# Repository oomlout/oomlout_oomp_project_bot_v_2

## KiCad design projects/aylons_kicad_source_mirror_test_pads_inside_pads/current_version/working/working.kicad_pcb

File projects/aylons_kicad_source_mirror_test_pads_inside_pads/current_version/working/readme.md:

# kicad_source_mirror
 
## summary 
* id: aylons_kicad_source_mirror_test_pads_inside_pads
* user: aylons
* name: kicad_source_mirror
* board: test_pads_inside_pads
* repo: https://github.com/aylons/kicad-source-mirror
* src_file_repo_kicad_pcb: demos/test_pads_inside_pads/test_pads_inside_pads.kicad_pcb
* src_file_repo_kicad_pcb_link: https://github.com/aylons/kicad-source-mirror/tree/master/demos/test_pads_inside_pads/test_pads_inside_pads.kicad_pcb

* src_file_repo_sch: demos/test_pads_inside_pads/test_pads_inside_pads.sch
* src_file_repo_sch_link: https://github.com/aylons/kicad-source-mirror/tree/master/demos/test_pads_inside_pads/test_pads_inside_pads.sch
* full details link: https://github.com/oomlout/oomlout_oomp_project_bot_v_2/tree/main/projects/aylons_kicad_source_mirror_test_pads_inside_pads/current_version/working

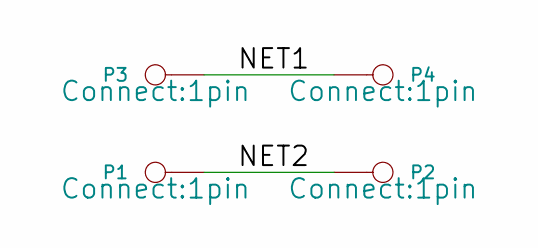
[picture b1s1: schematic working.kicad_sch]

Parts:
P1, P2, P3, P4: CONN_1; 1pin

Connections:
/NET1: P3.1, P4.1
/NET2: P1.1, P2.1

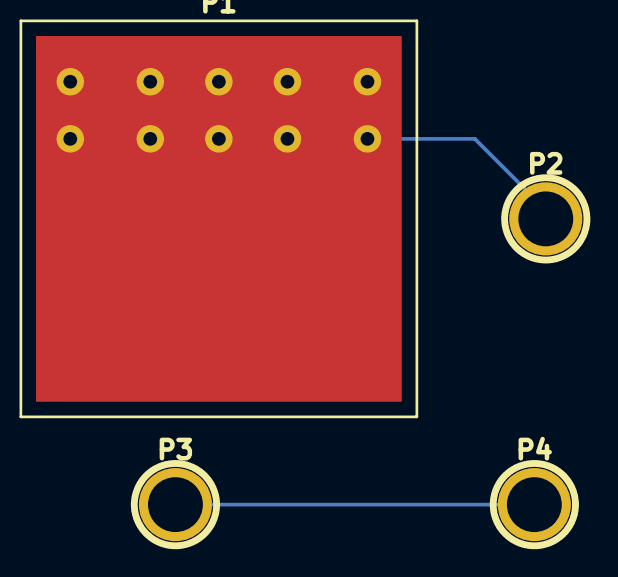
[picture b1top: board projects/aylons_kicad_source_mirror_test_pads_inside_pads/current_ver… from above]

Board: 2 copper layers, 4 parts (0 on the bottom side), 2 nets.

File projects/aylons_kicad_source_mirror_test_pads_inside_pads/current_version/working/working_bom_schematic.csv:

"Source:","C:\gh\oomlout_oomp_project_bot_v_2\projects\aylons_kicad_source_mirror_test_pads_inside_pads\current_version\working\working.kicad_sch"
"Date:","27/09/2023 15:33:38"
"Tool:","Eeschema 7.0.6"
"Generator:","C:/Program Files/KiCad/7.0/bin/scripting/plugins/bom_csv_grouped_by_value_with_fp.py"
"Component Count:","4"
"Ref","Qnty","Value","Cmp name","Footprint","Description","Vendor","DNP"
"P1, P2, P3, P4","4","CONN_1","CONN_1","Connect:1pin","","",""

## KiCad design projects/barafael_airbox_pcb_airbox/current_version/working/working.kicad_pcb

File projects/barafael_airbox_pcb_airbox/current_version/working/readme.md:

# airbox_pcb
 
## summary 
* id: barafael_airbox_pcb_airbox
* user: barafael
* name: airbox_pcb
* board: airbox
* repo: https://github.com/barafael/airbox-pcb
* src_file_repo_kicad_pcb: airbox.kicad_pcb
* src_file_repo_kicad_pcb_link: https://github.com/barafael/airbox-pcb/tree/main/airbox.kicad_pcb

* src_file_repo_sch: airbox.sch
* src_file_repo_sch_link: https://github.com/barafael/airbox-pcb/tree/main/airbox.sch
* full details link: https://github.com/oomlout/oomlout_oomp_project_bot_v_2/tree/main/projects/barafael_airbox_pcb_airbox/current_version/working

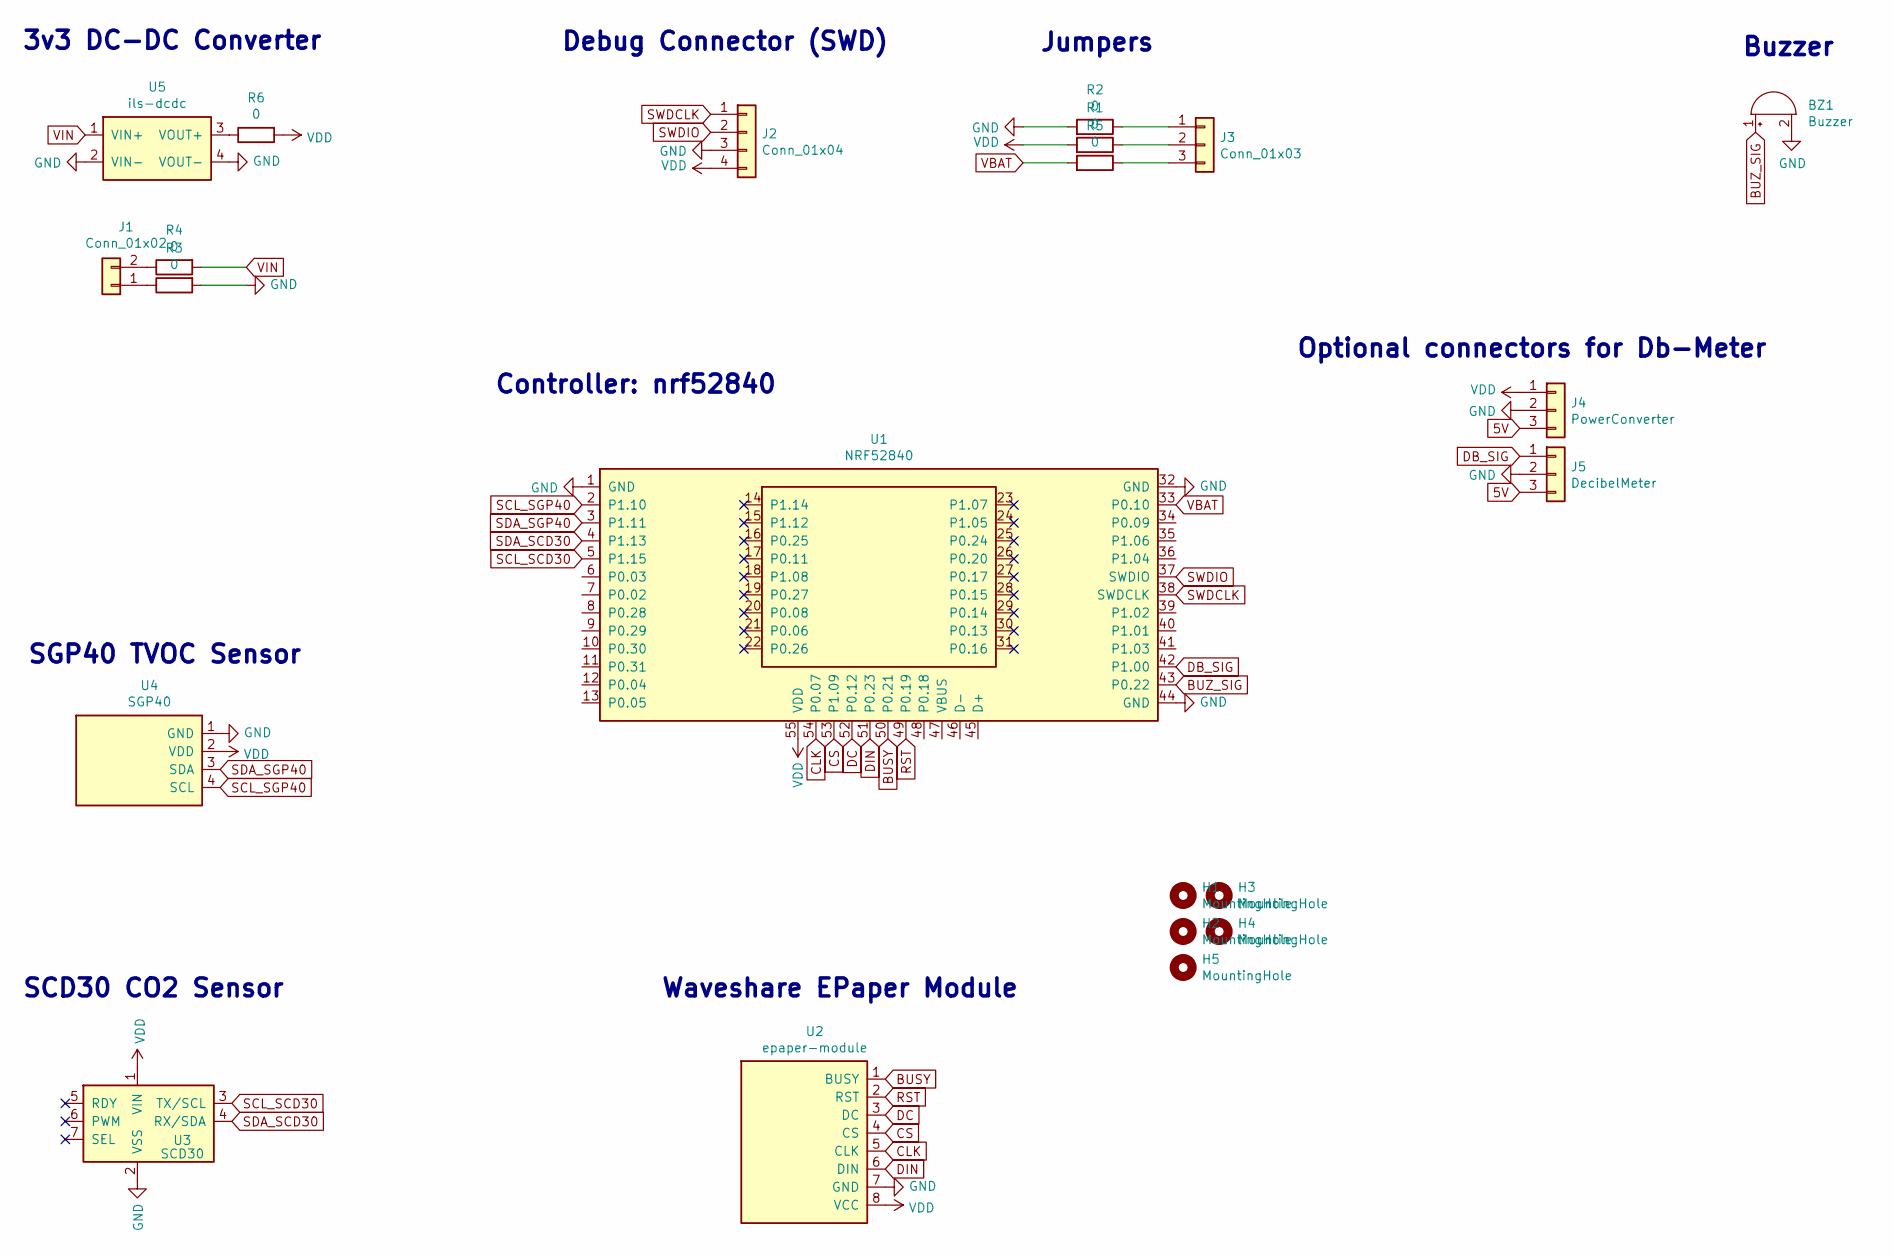
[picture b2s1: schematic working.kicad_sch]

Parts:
BZ1: Buzzer; PS1240P02BT
H1, H2, H3, H4, H5: MountingHole; MountingHole_3mm
J1: Conn_01x02; JST_EH_B2B-EH-A_1x02_P2.50mm_Vertical
J2: Conn_01x04; JST_EH_B4B-EH-A_1x04_P2.50mm_Vertical
J3: Conn_01x03; JST_EH_B3B-EH-A_1x03_P2.50mm_Vertical
J4: PowerConverter; PinSocket_1x03_P2.54mm_Vertical
J5: DecibelMeter; PinSocket_1x03_P2.54mm_Vertical
R1, R2, R3, R4, R5, R6: 0; R_0805_2012Metric
U1: NRF52840; nrf52-waveshare
U2: epaper-module
U3: SCD30; scd30
U4: SGP40; sgp40-sparkx-breakout
U5: ils-dcdc; ils-3v3dcdc

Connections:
5V: J4.3, J5.3
BUSY: U1.50 (P0.21), U2.1 (BUSY)
BUZ_SIG: BZ1.1 (-), U1.43 (P0.22)
CLK: U1.54 (P0.07), U2.5 (CLK)
CS: U1.53 (P1.09), U2.4 (CS)
DB_SIG: J5.1, U1.42 (P1.00)
DC: U1.52 (P0.12), U2.3 (DC)
DIN: U1.51 (P0.23), U2.6 (DIN)
GND: BZ1.2 (+), J2.3, J4.2, J5.2, R2.2, R3.2, U1.1 (GND), U1.32 (GND), U1.44 (GND), U2.7 (GND), U3.2 (VSS), U4.1 (GND), U5.2 (VIN-), U5.4 (VOUT-)
unnamed: J1.1, R3.1
unnamed: J1.2, R4.1
unnamed: J3.1, R2.1
unnamed: J3.2, R1.1
unnamed: J3.3, R5.1
unnamed: R6.1, U5.3 (VOUT+)
RST: U1.49 (P0.19), U2.2 (RST)
SCL_SCD30: U1.5 (P1.15), U3.3 (TX/SCL)
SCL_SGP40: U1.2 (P1.10), U4.4 (SCL)
SDA_SCD30: U1.4 (P1.13), U3.4 (RX/SDA)
SDA_SGP40: U1.3 (P1.11), U4.3 (SDA)
SWDCLK: J2.1, U1.38 (SWDCLK)
SWDIO: J2.2, U1.37 (SWDIO)
VBAT: R5.2, U1.33 (P0.10)
VDD: J2.4, J4.1, R1.2, R6.2, U1.55 (VDD), U2.8 (VCC), U3.1 (VIN), U4.2 (VDD)
VIN: R4.2, U5.1 (VIN+)

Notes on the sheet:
Optional connectors for Db-Meter
Jumpers
Buzzer
Controller: nrf52840
Debug Connector (SWD)
Waveshare EPaper Module
SGP40 TVOC Sensor
3v3 DC-DC Converter
SCD30 CO2 Sensor

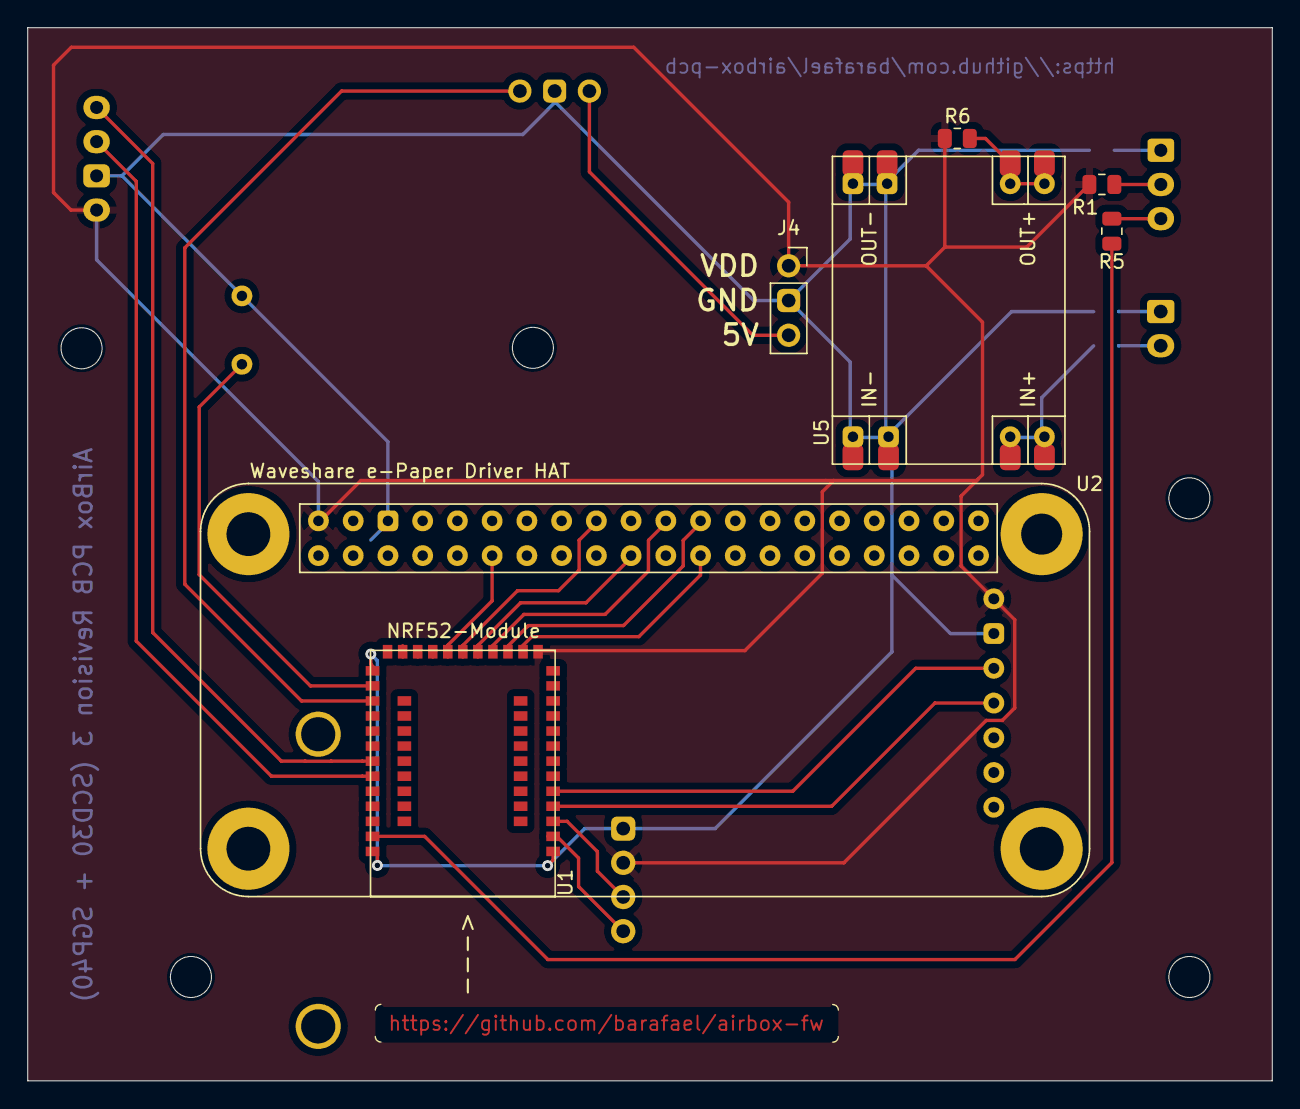
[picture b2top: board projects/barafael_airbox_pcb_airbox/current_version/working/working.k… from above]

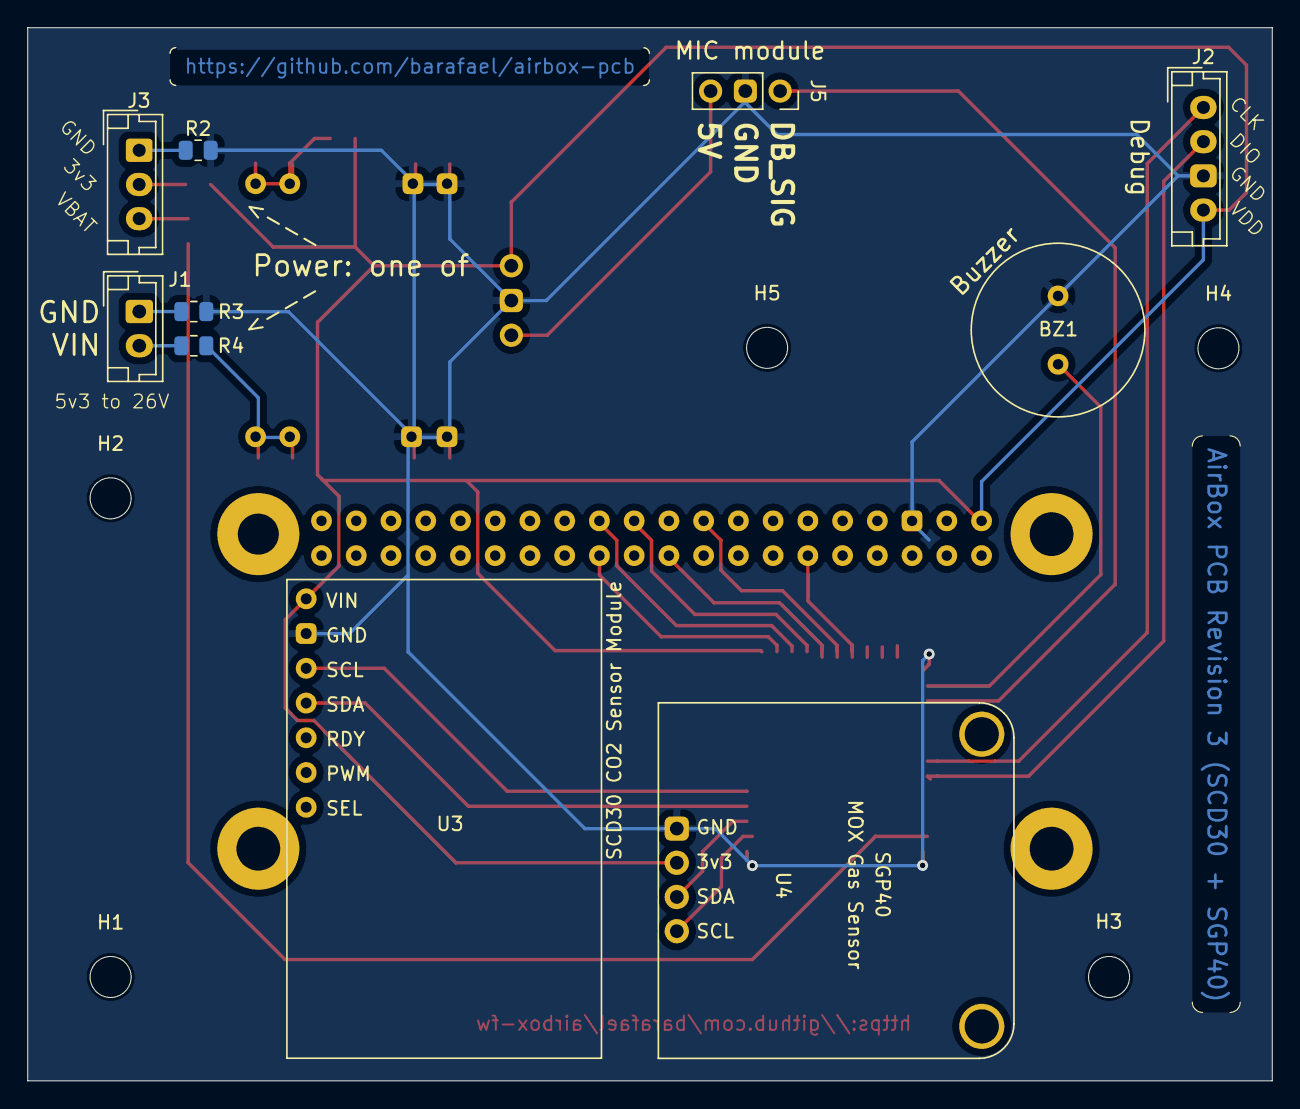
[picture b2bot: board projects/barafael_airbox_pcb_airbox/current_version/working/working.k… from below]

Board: 2 copper layers, 91.0 x 77.0 mm, 22 parts (10 on the bottom side), 25 nets.

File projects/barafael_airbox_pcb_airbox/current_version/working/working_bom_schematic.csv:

"Source:","C:\gh\oomlout_oomp_project_bot_v_2\projects\barafael_airbox_pcb_airbox\current_version\working\working.kicad_sch"
"Date:","27/09/2023 15:47:06"
"Tool:","Eeschema 7.0.6"
"Generator:","C:/Program Files/KiCad/7.0/bin/scripting/plugins/bom_csv_grouped_by_value_with_fp.py"
"Component Count:","22"
"Ref","Qnty","Value","Cmp name","Footprint","Description","Vendor","DNP"
"BZ1","1","Buzzer","Buzzer","PS1240P02BT:PS1240P02BT","Buzzer, polarized","",""
"H1, H2, H3, H4, H5","5","MountingHole","MountingHole","MountingHole:MountingHole_3mm","Mounting Hole without connection","",""
"J1","1","Conn_01x02","Conn_01x02","Connector_JST:JST_EH_B2B-EH-A_1x02_P2.50mm_Vertical","Generic connector, single row, 01x02, script generated (kicad-library-utils/schlib/autogen/connector/)","",""
"J2","1","Conn_01x04","Conn_01x04","Connector_JST:JST_EH_B4B-EH-A_1x04_P2.50mm_Vertical","Generic connector, single row, 01x04, script generated (kicad-library-utils/schlib/autogen/connector/)","",""
"J3","1","Conn_01x03","Conn_01x03","Connector_JST:JST_EH_B3B-EH-A_1x03_P2.50mm_Vertical","Generic connector, single row, 01x03, script generated (kicad-library-utils/schlib/autogen/connector/)","",""
"J4","1","PowerConverter","Conn_01x03","Connector_PinSocket_2.54mm:PinSocket_1x03_P2.54mm_Vertical","Generic connector, single row, 01x03, script generated (kicad-library-utils/schlib/autogen/connector/)","",""
"J5","1","DecibelMeter","Conn_01x03","Connector_PinSocket_2.54mm:PinSocket_1x03_P2.54mm_Vertical","Generic connector, single row, 01x03, script generated (kicad-library-utils/schlib/autogen/connector/)","",""
"R1, R2, R3, R4, R5, R6","6","0","R","Resistor_SMD:R_0805_2012Metric","Resistor","",""
"U1","1","NRF52840","NRF52840-nrf52-waveshare","nrf52840-waveshare:nrf52-waveshare","","",""
"U2","1","epaper-module","epaper-module-epaper-module","waveshare-epaper-module:epaper-module","","",""
"U3","1","SCD30","SCD30-scd30","sensirion-scd30:scd30","","",""
"U4","1","SGP40","SGP40-sgp40","sgp40-adafruit-breakout:sgp40-sparkx-breakout","","",""
"U5","1","ils-dcdc","ils-dcdc","ils-dcdc:ils-3v3dcdc","","",""

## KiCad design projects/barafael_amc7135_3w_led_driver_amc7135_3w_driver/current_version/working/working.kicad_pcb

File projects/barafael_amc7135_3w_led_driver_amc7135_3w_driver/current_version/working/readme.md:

# amc7135_3w_led_driver
 
## summary 
* id: barafael_amc7135_3w_led_driver_amc7135_3w_driver
* user: barafael
* name: amc7135_3w_led_driver
* board: amc7135_3w_driver
* repo: https://github.com/barafael/amc7135-3W-LED-driver
* src_file_repo_kicad_pcb: amc7135_3w_driver.kicad_pcb
* src_file_repo_kicad_pcb_link: https://github.com/barafael/amc7135-3W-LED-driver/tree/master/amc7135_3w_driver.kicad_pcb

* src_file_repo_sch: amc7135_3w_driver.sch
* src_file_repo_sch_link: https://github.com/barafael/amc7135-3W-LED-driver/tree/master/amc7135_3w_driver.sch
* full details link: https://github.com/oomlout/oomlout_oomp_project_bot_v_2/tree/main/projects/barafael_amc7135_3w_led_driver_amc7135_3w_driver/current_version/working

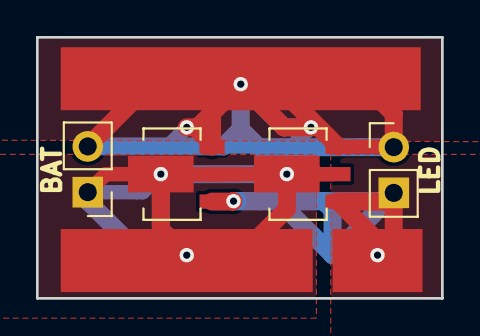
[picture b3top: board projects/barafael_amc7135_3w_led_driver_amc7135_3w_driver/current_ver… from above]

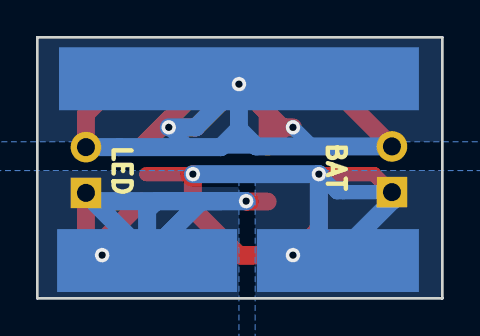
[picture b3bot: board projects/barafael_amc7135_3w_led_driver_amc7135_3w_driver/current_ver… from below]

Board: 2 copper layers, 22.5 x 14.5 mm, 10 parts (3 on the bottom side), 3 nets.

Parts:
J1: LED connector; PinHeader_1x02_P2.54mm_Vertical
J2: Power Connector; PinHeader_1x02_P2.54mm_Vertical
J3, J4#2, J5#2: Conn_01x01_Male; Pin_D1.0mm_L10.0mm_LooseFit
J3#2, J4, J5: heatsink; Pin_D1.0mm_L10.0mm_LooseFit
U1, U2: AMC7135_SOT89; SOT89

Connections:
GND: J2.1, J4.1, J4#2.1, U1.2, U2.2
unnamed: J1.2, J5.1, J5#2.1, U1.1, U2.1
VDD: J1.1, J2.2, J3.1, J3#2.1, U1.3, U2.3

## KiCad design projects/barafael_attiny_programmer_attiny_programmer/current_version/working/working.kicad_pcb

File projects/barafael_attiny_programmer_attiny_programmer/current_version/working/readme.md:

# attiny_programmer
 
## summary 
* id: barafael_attiny_programmer_attiny_programmer
* user: barafael
* name: attiny_programmer
* board: attiny_programmer
* repo: https://github.com/barafael/attiny-programmer
* src_file_repo_kicad_pcb: attiny-programmer.kicad_pcb
* src_file_repo_kicad_pcb_link: https://github.com/barafael/attiny-programmer/tree/master/attiny-programmer.kicad_pcb

* src_file_repo_sch: attiny-programmer.sch
* src_file_repo_sch_link: https://github.com/barafael/attiny-programmer/tree/master/attiny-programmer.sch
* full details link: https://github.com/oomlout/oomlout_oomp_project_bot_v_2/tree/main/projects/barafael_attiny_programmer_attiny_programmer/current_version/working

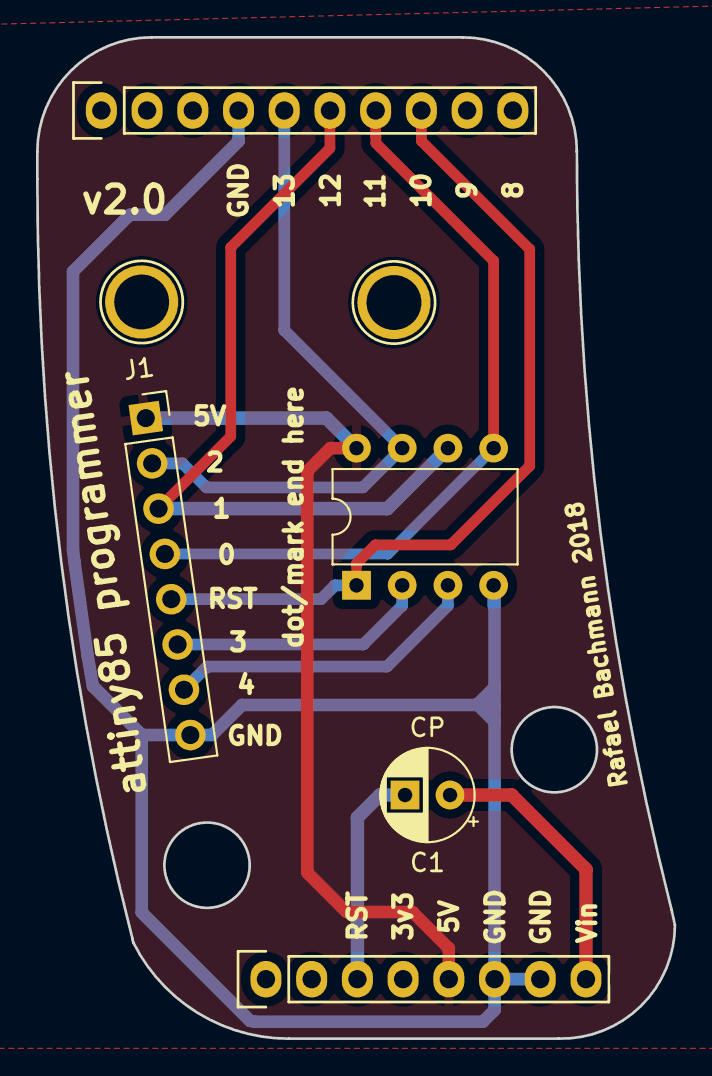
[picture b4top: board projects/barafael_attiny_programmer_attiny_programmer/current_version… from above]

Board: 2 copper layers, 35.4 x 55.6 mm, 7 parts (0 on the bottom side), 10 nets.

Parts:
C1: CP; CP_Radial_D5.0mm_P2.50mm
J1: Conn_01x08; PinSocket_1x08_P2.54mm_Vertical
P1: Power; Socket_Strip_Arduino_1x08
P3: Digital; Socket_Strip_Arduino_1x10
P7, P8: CONN_01X01; Arduino_1pin
U1: ATtiny85-20PU; DIP-8_W7.62mm

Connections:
+5V: J1.1, P1.5, U1.8
/10(**/SS): J1.5, P3.8, U1.1
/11(**/MOSI): J1.4, P3.7, U1.5
/12(MISO): J1.3, P3.6, U1.6
/13(SCK): J1.2, P3.5, U1.7
/Reset: C1.2, P1.3
/Vin: C1.1, P1.8
GND: J1.8, P1.6, P1.7, P3.4, U1.4
unnamed: J1.6, U1.2
unnamed: J1.7, U1.3

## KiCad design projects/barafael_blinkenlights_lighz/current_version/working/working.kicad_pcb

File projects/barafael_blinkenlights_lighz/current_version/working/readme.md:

# blinkenlights
 
## summary 
* id: barafael_blinkenlights_lighz
* user: barafael
* name: blinkenlights
* board: lighz
* repo: https://github.com/barafael/blinkenlights
* src_file_repo_kicad_pcb: board/lighz.kicad_pcb
* src_file_repo_kicad_pcb_link: https://github.com/barafael/blinkenlights/tree/master/board/lighz.kicad_pcb

* src_file_repo_sch: 
* src_file_repo_sch_link: https://github.com/barafael/blinkenlights/tree/master/
* full details link: https://github.com/oomlout/oomlout_oomp_project_bot_v_2/tree/main/projects/barafael_blinkenlights_lighz/current_version/working

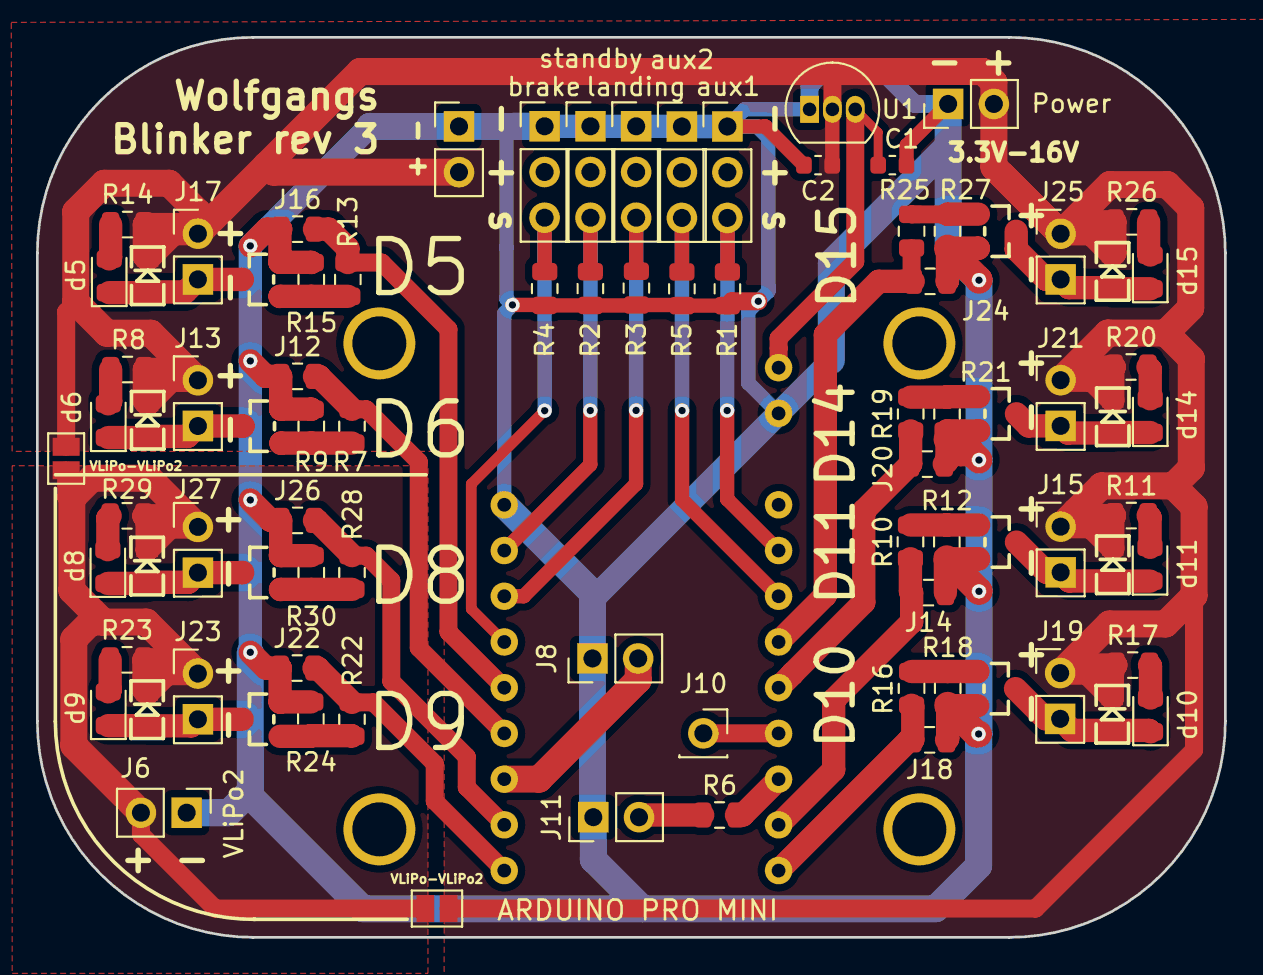
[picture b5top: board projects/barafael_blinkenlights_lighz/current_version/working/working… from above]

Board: 2 copper layers, 66.0 x 50.0 mm, 91 parts (0 on the bottom side), 45 nets.

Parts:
1pin_prototyping, 1pin_prototyping#2, 1pin_prototyping#3, 1pin_prototyping#4: val**; 1pin_prototyping
C1, C2: C; C_0603_1608Metric
D2, D4, D6, D8, D10, D12, D14, D16: DIODE; LED-0805
J1: aux1; PinHeader_1x03_P2.54mm_Vertical
J2: brake; PinHeader_1x03_P2.54mm_Vertical
J3: aux2; PinHeader_1x03_P2.54mm_Vertical
J4: standby; PinHeader_1x03_P2.54mm_Vertical
J5: landing; PinHeader_1x03_P2.54mm_Vertical
J6: VLiPo2; PinHeader_1x02_P2.54mm_Vertical
J7: vlipo; PinHeader_1x02_P2.54mm_Vertical
J8: dbg2; PinHeader_1x02_P2.54mm_Vertical
J10: DBG_PIN; PinSocket_1x01_P2.54mm_Vertical
J11: buzz; PinHeader_1x02_P2.54mm_Vertical
J12, J14, J16, J18, J20, J22, J24, J26: Conn_01x02_Female; R_0805_2012Metric
J13, J15, J17, J19, J21, J23, J25, J27: output; PinHeader_1x02_P2.54mm_Vertical
Power: power; PinHeader_1x02_P2.54mm_Vertical
Q1, Q2, Q3, Q4, Q5, Q6, Q7, Q8: MOSFET_N; SOT23_FET
R1, R2, R3, R4, R5: R; R_0805_2012Metric
R6: 100; R_0805_2012Metric
R7, R10, R13, R16, R19, R22, R25, R28: 1k; R_0805_2012Metric
R8, R11, R14, R17, R20, R23, R26, R29: 500; R_0805_2012Metric
R9, R12, R15, R18, R21, R24, R27, R30: 100k; R_0805_2012Metric
U1: MCP1700-5002E_TO92; TO-92_Inline
VLiPo-VLiPo2, VLiPo-VLiPo2#2: R; SolderJumper-2_P1.3mm_Open_Pad1.0x1.5mm
d5, d6, d8, d9, d10, d11, d14, d15: LED; LED_0805_2012Metric
uP1: ARDUINO PRO MINI; ArduProMini-6

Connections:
D5_sig: J16.2, R13.2, uP1.14
D6_sig: J12.2, R7.2, uP1.15
D8_sig: J26.2, R28.2, uP1.17
D9_sig: J22.2, R22.2, uP1.18
D10_sig: J18.2, R16.2, uP1.30
D11_sig: J14.2, R10.2, uP1.29
D14_sig: J20.2, R19.2, uP1.26
D15_sig: J24.2, R25.2, uP1.25
GND: C1.2, C2.2, J1.1, J2.1, J3.1, J4.1, J5.1, J6.1, J7.1, J8.1, J11.1, J12.1, J14.1, J16.1, J18.1, J20.1, J22.1, J24.1, J26.1, Power.1, Q1.S, Q2.S, Q3.S, Q4.S, Q5.S, Q6.S, Q7.S, Q8.S, R1.2, R2.2, R3.2, R4.2, R5.2, R9.1, R12.1, R15.1, R18.1, R21.1, R24.1, R27.1, R30.1, U1.1, uP1.10, uP1.20
unnamed: C1.1, U1.3, uP1.19
unnamed: D2.A, J13.2, Q1.D, d6.1
unnamed: R8.2, d6.2
unnamed: D4.A, J15.2, Q2.D, d11.1
unnamed: R11.2, d11.2
unnamed: D6.A, J17.2, Q3.D, d5.1
unnamed: R14.2, d5.2
unnamed: D8.A, J19.2, Q4.D, d10.1
unnamed: R17.2, d10.2
unnamed: R20.2, d14.2
unnamed: D10.A, J21.2, Q5.D, d14.1
unnamed: D12.A, J23.2, Q6.D, d9.1
unnamed: R23.2, d9.2
unnamed: D14.A, J25.2, Q7.D, d15.1
unnamed: R26.2, d15.2
unnamed: D16.A, J27.2, Q8.D, d8.1
unnamed: R29.2, d8.2
unnamed: J1.3, R1.1, uP1.23
unnamed: J2.3, R4.1, uP1.13
unnamed: J3.3, R5.1, uP1.24
unnamed: J4.3, R2.1, uP1.11
unnamed: J5.3, R3.1, uP1.12
unnamed: J8.2, uP1.16
unnamed: J10.1, uP1.27
unnamed: J11.2, R6.1
unnamed: Q1.G, R7.1, R9.2
unnamed: Q2.G, R10.1, R12.2
unnamed: Q3.G, R13.1, R15.2
unnamed: Q4.G, R16.1, R18.2
unnamed: Q5.G, R19.1, R21.2
unnamed: Q6.G, R22.1, R24.2
unnamed: Q7.G, R25.1, R27.2
unnamed: Q8.G, R28.1, R30.2
unnamed: R6.2, uP1.28
VLiPo: C2.1, D2.K, D4.K, D6.K, D8.K, D10.K, D14.K, J7.2, J13.1, J15.1, J17.1, J19.1, J21.1, J25.1, Power.2, R8.1, R11.1, R14.1, R17.1, R20.1, R26.1, U1.2, VLiPo-VLiPo2.1, VLiPo-VLiPo2#2.1
VLiPo2: D12.K, D16.K, J6.2, J23.1, J27.1, R23.1, R29.1, VLiPo-VLiPo2.2, VLiPo-VLiPo2#2.2

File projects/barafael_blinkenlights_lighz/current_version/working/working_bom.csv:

"Id";"Designator";"Footprint";"Quantity";"Designation";"Supplier and ref";
1;"d6,d5,d9,d8,d15,d14,d11,d10";"LED_0805_2012Metric";8;"LED";;;
2;"D2,D6,D12,D16,D8,D4,D10,D14";"LED-0805";8;"DIODE";;;
3;"J2";"PinHeader_1x03_P2.54mm_Vertical";1;"brake";;;
4;"J4";"PinHeader_1x03_P2.54mm_Vertical";1;"standby";;;
5;"Power";"PinHeader_1x02_P2.54mm_Vertical";1;"power";;;
6;"J10";"PinSocket_1x01_P2.54mm_Vertical";1;"DBG_PIN";;;
7;"J6";"PinHeader_1x02_P2.54mm_Vertical";1;"VLiPo2";;;
8;"J7";"PinHeader_1x02_P2.54mm_Vertical";1;"vlipo";;;
9;"J11";"PinHeader_1x02_P2.54mm_Vertical";1;"buzz";;;
10;"J12,J16,J22,J26,J24,J20,J14,J18";"R_0805_2012Metric";8;"Conn_01x02_Female";;;
11;"J13,J17,J23,J27,J15,J19,J25,J21";"PinHeader_1x02_P2.54mm_Vertical";8;"output";;;
12;"Q1,Q3,Q6,Q8,Q2,Q5,Q4,Q7";"SOT23_FET";8;"MOSFET_N";;;
13;"R1,R2,R4,R5,R3";"R_0805_2012Metric";5;"R";;;
14;"R6";"R_0805_2012Metric";1;"100";;;
15;"R7,R13,R22,R28,R16,R10,R19,R25";"R_0805_2012Metric";8;"1k";;;
16;"R8,R14,R23,R29,R20,R26,R11,R17";"R_0805_2012Metric";8;"500";;;
17;"R9,R15,R24,R30,R27,R12,R21,R18";"R_0805_2012Metric";8;"100k";;;
18;"J1";"PinHeader_1x03_P2.54mm_Vertical";1;"aux1";;;
19;"J3";"PinHeader_1x03_P2.54mm_Vertical";1;"aux2";;;
20;"uP1";"ArduProMini-6";1;"ARDUINO PRO MINI";;;
21;"J5";"PinHeader_1x03_P2.54mm_Vertical";1;"landing";;;
22;"1pin_prototyping,1pin_prototyping,1pin_prototyping,1pin_prototyping";"1pin_prototyping";4;"val**";;;
23;"J8";"PinHeader_1x02_P2.54mm_Vertical";1;"dbg2";;;
24;"C1,C2";"C_0603_1608Metric";2;"C";;;
25;"U1";"TO-92_Inline";1;"MCP1700-5002E_TO92";;;

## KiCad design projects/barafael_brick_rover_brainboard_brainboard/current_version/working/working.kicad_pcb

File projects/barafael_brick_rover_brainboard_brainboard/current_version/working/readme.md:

# brick_rover_brainboard
 
## summary 
* id: barafael_brick_rover_brainboard_brainboard
* user: barafael
* name: brick_rover_brainboard
* board: brainboard
* repo: https://github.com/barafael/brick-rover-brainboard
* src_file_repo_kicad_pcb: board/brainboard.kicad_pcb
* src_file_repo_kicad_pcb_link: https://github.com/barafael/brick-rover-brainboard/tree/main/board/brainboard.kicad_pcb

* src_file_repo_sch: board/brainboard.sch
* src_file_repo_sch_link: https://github.com/barafael/brick-rover-brainboard/tree/main/board/brainboard.sch
* full details link: https://github.com/oomlout/oomlout_oomp_project_bot_v_2/tree/main/projects/barafael_brick_rover_brainboard_brainboard/current_version/working

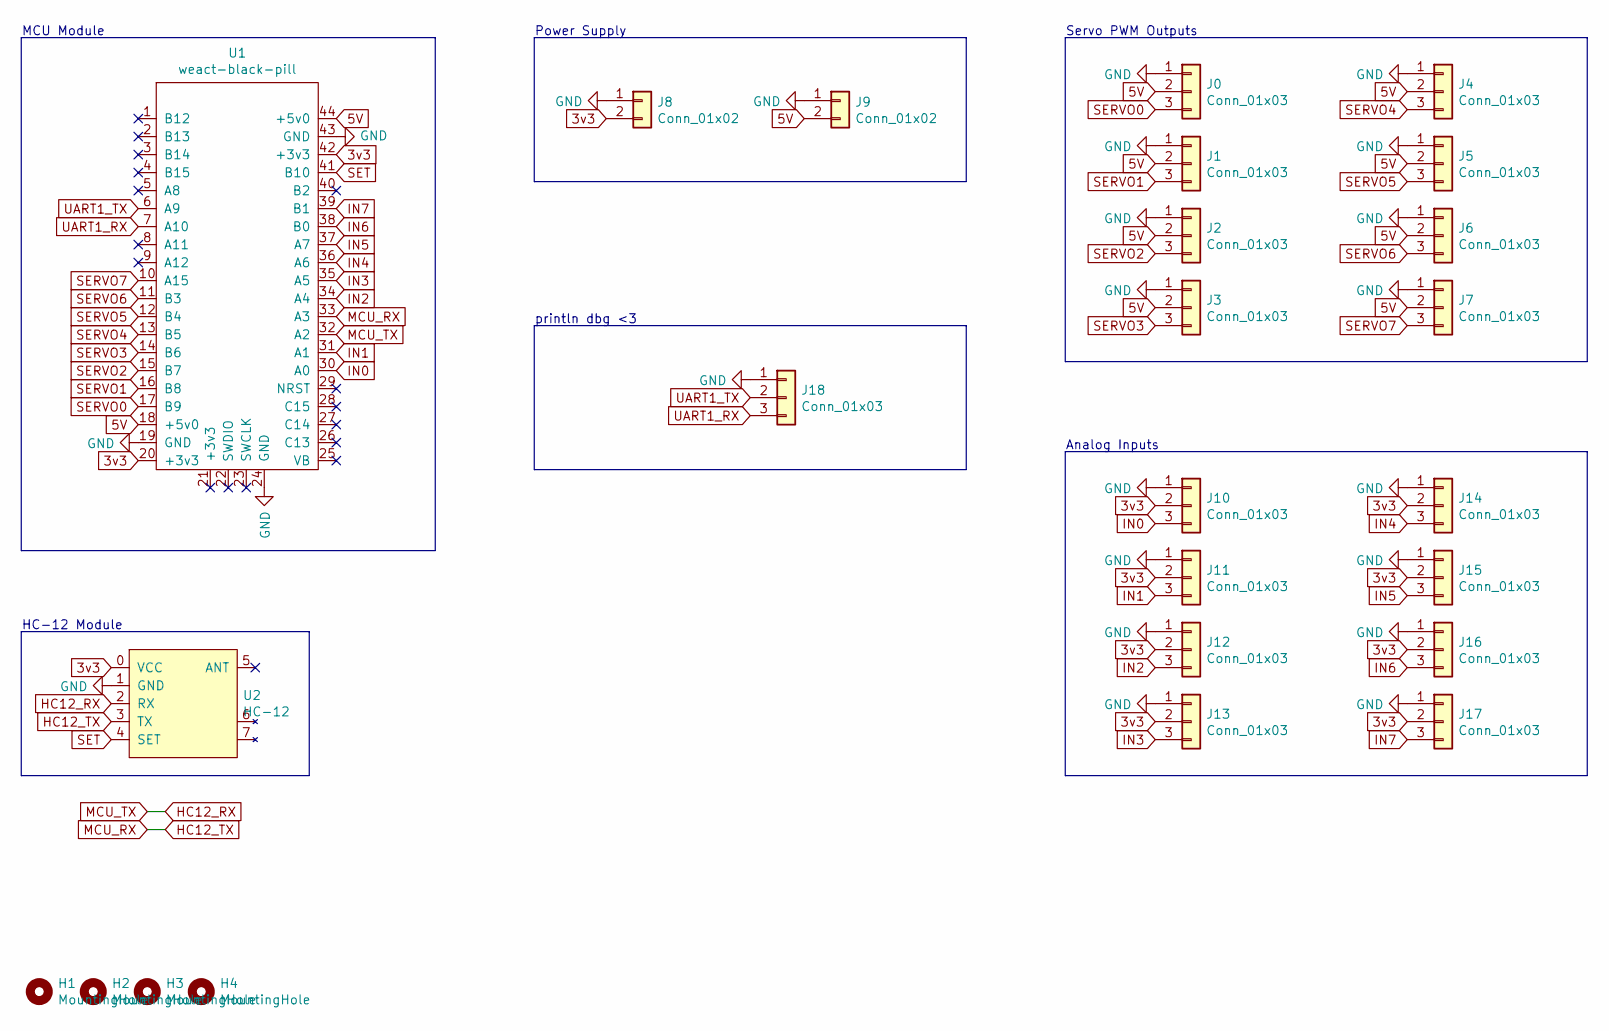
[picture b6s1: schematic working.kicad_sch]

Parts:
H1: MountingHole; weact-blackpill-nodebug
H2, H3, H4: MountingHole; MountingHole_3.2mm_M3
J0, J1, J2, J3, J4, J5, J6, J7, J10, J11, J12, J13, J14, J15, J16, J17: Conn_01x03; PinHeader_1x03_P2.54mm_Vertical
J8, J9: Conn_01x02; PinHeader_1x02_P2.54mm_Vertical
J18: Conn_01x03; PinSocket_1x03_P2.54mm_Vertical
U1: weact-black-pill; weact-blackpill
U2: HC-12; hc12-module

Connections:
3v3: J8.2, J10.2, J11.2, J12.2, J13.2, J14.2, J15.2, J16.2, J17.2, U1.20 (+3v3), U1.42 (+3v3), U2.0 (VCC)
5V: J0.2, J1.2, J2.2, J3.2, J4.2, J5.2, J6.2, J7.2, J9.2, U1.18 (+5v0), U1.44 (+5v0)
GND: J0.1, J1.1, J2.1, J3.1, J4.1, J5.1, J6.1, J7.1, J8.1, J9.1, J10.1, J11.1, J12.1, J13.1, J14.1, J15.1, J16.1, J17.1, J18.1, U1.19 (GND), U1.24 (GND), U1.43 (GND), U2.1 (GND)
HC12_RX: U1.32 (A2), U2.2 (RX)
HC12_TX: U1.33 (A3), U2.3 (TX)
IN0: J10.3, U1.30 (A0)
IN1: J11.3, U1.31 (A1)
IN2: J12.3, U1.34 (A4)
IN3: J13.3, U1.35 (A5)
IN4: J14.3, U1.36 (A6)
IN5: J15.3, U1.37 (A7)
IN6: J16.3, U1.38 (B0)
IN7: J17.3, U1.39 (B1)
SERVO0: J0.3, U1.17 (B9)
SERVO1: J1.3, U1.16 (B8)
SERVO2: J2.3, U1.15 (B7)
SERVO3: J3.3, U1.14 (B6)
SERVO4: J4.3, U1.13 (B5)
SERVO5: J5.3, U1.12 (B4)
SERVO6: J6.3, U1.11 (B3)
SERVO7: J7.3, U1.10 (A15)
SET: U1.41 (B10), U2.4 (SET)
UART1_RX: J18.3, U1.7 (A10)
UART1_TX: J18.2, U1.6 (A9)

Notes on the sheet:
Power Supply
HC-12 Module
Analog Inputs
println dbg <3
MCU Module
Servo PWM Outputs

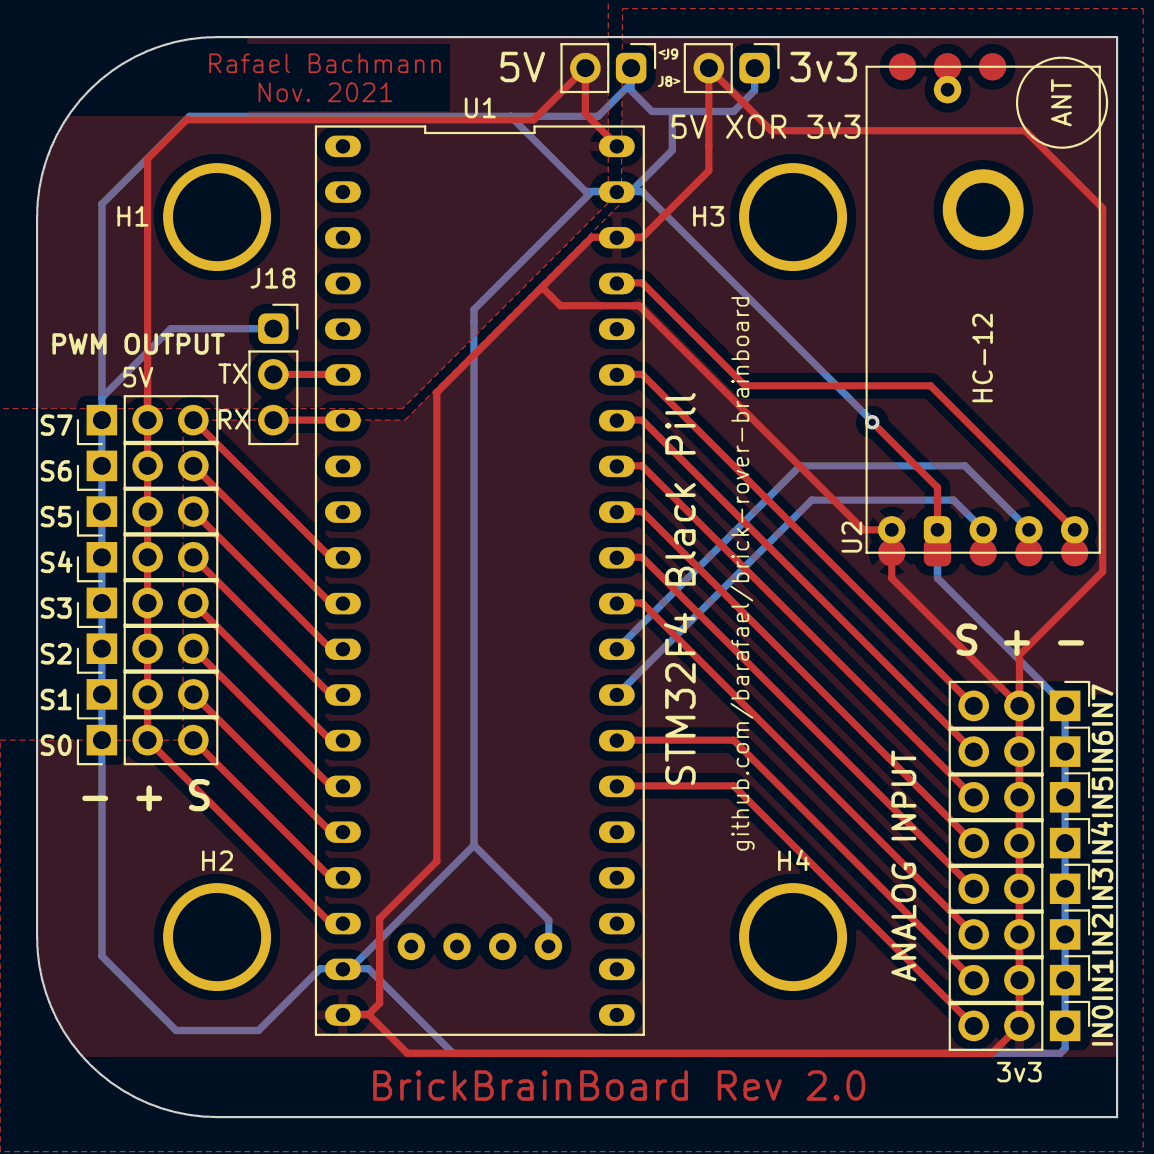
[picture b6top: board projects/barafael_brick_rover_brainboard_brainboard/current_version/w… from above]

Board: 2 copper layers, 60.0 x 60.0 mm, 25 parts (0 on the bottom side), 24 nets.

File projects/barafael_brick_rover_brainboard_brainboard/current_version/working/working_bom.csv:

"Id";"Designator";"Footprint";"Quantity";"Designation";"Supplier and ref";
1;"J0,J1,J6,J7,J4,J5,J2,J3,J10,J11,J12,J13,J14,J15,J16,J17";"PinHeader_1x03_P2.54mm_Vertical";16;"Conn_01x03";;;
2;"J8,J9";"PinHeader_1x02_P2.54mm_Vertical";2;"Conn_01x02";;;
3;"U2";"hc12-module";1;"HC-12";;;
4;"U1";"weact-blackpill";1;"weact-black-pill";;;
5;"J18";"PinSocket_1x03_P2.54mm_Vertical";1;"Conn_01x03";;;

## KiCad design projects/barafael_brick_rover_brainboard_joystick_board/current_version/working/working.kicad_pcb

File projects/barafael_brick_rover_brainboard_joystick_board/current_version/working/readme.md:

# brick_rover_brainboard
 
## summary 
* id: barafael_brick_rover_brainboard_joystick_board
* user: barafael
* name: brick_rover_brainboard
* board: joystick_board
* repo: https://github.com/barafael/brick-rover-brainboard
* src_file_repo_kicad_pcb: joystick-board/joystick-board/joystick-board.kicad_pcb
* src_file_repo_kicad_pcb_link: https://github.com/barafael/brick-rover-brainboard/tree/main/joystick-board/joystick-board/joystick-board.kicad_pcb

* src_file_repo_sch: joystick-board/joystick-board/joystick-board.sch
* src_file_repo_sch_link: https://github.com/barafael/brick-rover-brainboard/tree/main/joystick-board/joystick-board/joystick-board.sch
* full details link: https://github.com/oomlout/oomlout_oomp_project_bot_v_2/tree/main/projects/barafael_brick_rover_brainboard_joystick_board/current_version/working

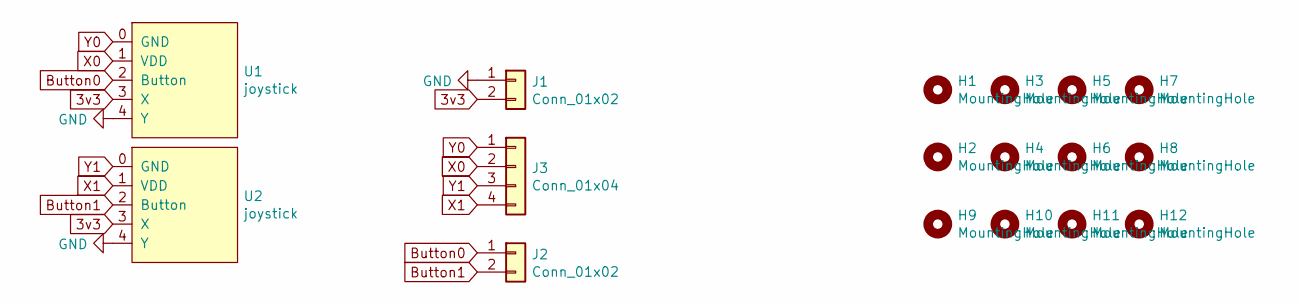
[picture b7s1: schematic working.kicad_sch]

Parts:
H1, H2, H3, H4, H5, H6, H7, H8, H9, H10, H11, H12: MountingHole; MountingHole_4mm
J1, J2: Conn_01x02; PinHeader_1x02_P2.54mm_Vertical
J3: Conn_01x04; PinHeader_1x04_P2.54mm_Vertical
U1, U2: joystick

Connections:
3v3: J1.2, U1.3 (X), U2.3 (X)
Button0: J2.1, U1.2 (Button)
Button1: J2.2, U2.2 (Button)
GND: J1.1, U1.4 (Y), U2.4 (Y)
X0: J3.2, U1.1 (VDD)
X1: J3.4, U2.1 (VDD)
Y0: J3.1, U1.0 (GND)
Y1: J3.3, U2.0 (GND)

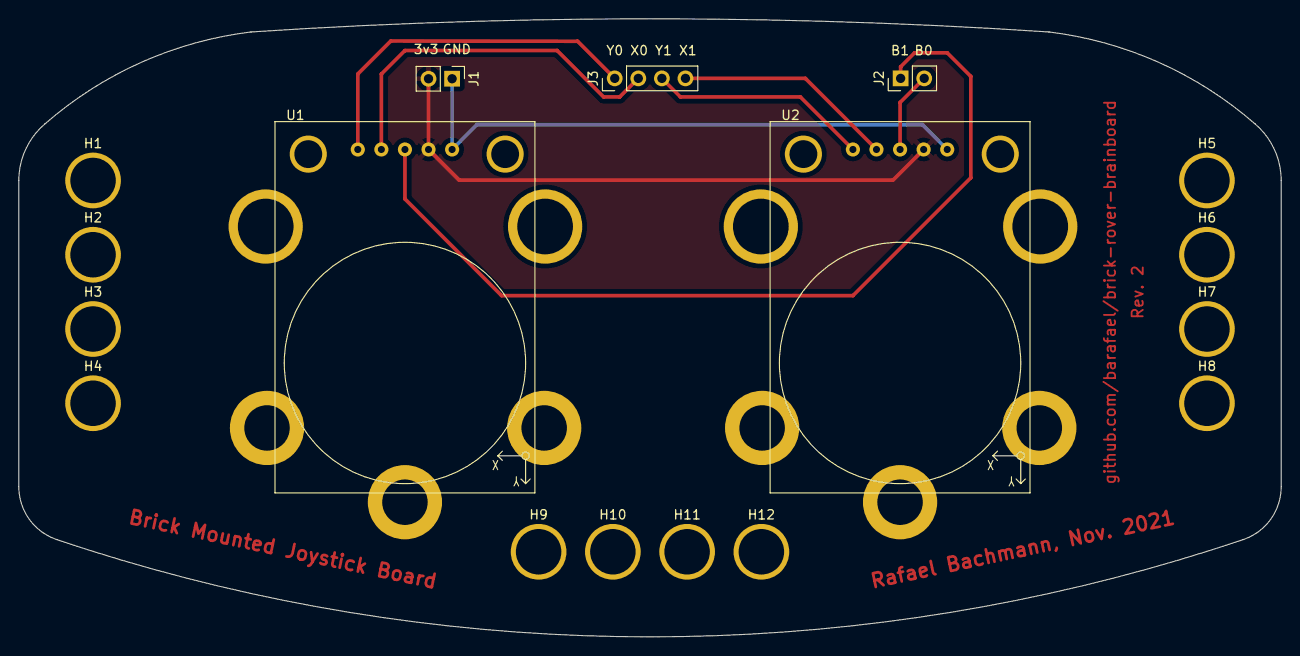
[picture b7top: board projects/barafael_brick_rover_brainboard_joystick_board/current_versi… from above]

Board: 2 copper layers, 136.0 x 66.6 mm, 17 parts (0 on the bottom side), 8 nets.

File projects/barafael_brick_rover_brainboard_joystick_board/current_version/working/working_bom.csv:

"Id";"Designator";"Footprint";"Quantity";"Designation";"Supplier and ref";
1;"J1,J2";"PinHeader_1x02_P2.54mm_Vertical";2;"Conn_01x02";;;
2;"U2,U1";"joystick";2;"joystick";;;
3;"J3";"PinHeader_1x04_P2.54mm_Vertical";1;"Conn_01x04";;;
